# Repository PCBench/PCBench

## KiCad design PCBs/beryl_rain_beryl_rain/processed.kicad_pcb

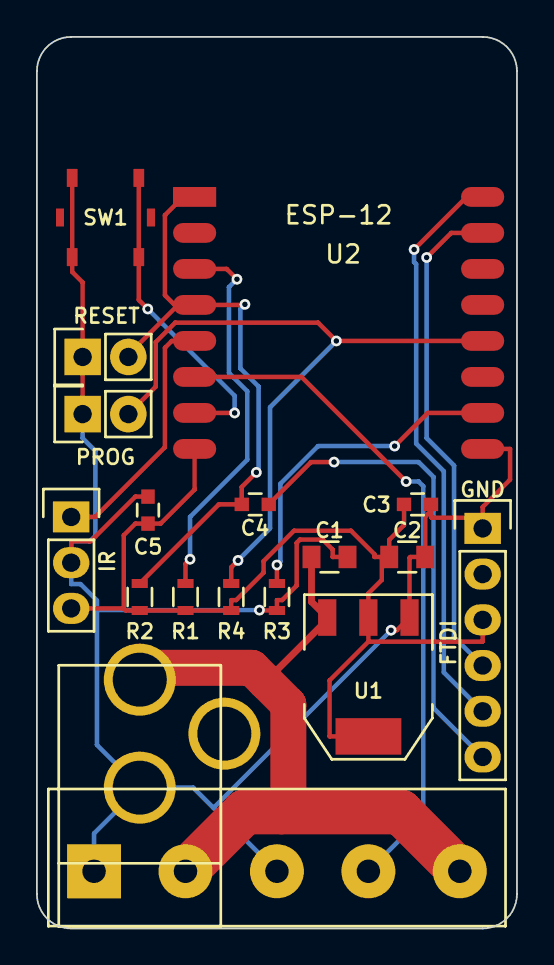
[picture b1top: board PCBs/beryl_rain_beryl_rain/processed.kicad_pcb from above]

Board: 2 copper layers, 26.7 x 49.5 mm, 18 parts (0 on the bottom side), 13 nets.

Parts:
C1, C2: CP; C_0805
C3, C4, C5: 0.1uF; C_0603
CON1: POWER; BARREL_JACK
P1: POWER; Terminal_Block_5.08mm_x5
P2: FTDI; Pin_Header_Straight_1x06
P3: IR; Pin_Header_Straight_1x03
P4: RESET; Pin_Header_Straight_1x02
P5: PROG; Pin_Header_Straight_1x02
R1, R2, R3, R4: 10K; R_0603
SW1: SWITCH; EVQPT5
U1: NCP1117ST33T3G; SOT-223
U2: ESP-12

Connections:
+3V3: C2.1, C3.1, C5.1, P2.3, P3.3, R1.1, R2.1, R4.1, U1.2, U1.4, U2.8
+5V: C1.1, CON1.1, P1.2, P1.5, U1.3
GND: C1.2, C2.2, C3.2, C5.2, CON1.2, P1.1, P1.3, P2.1, P3.2, P4.1, P5.1, R3.2, SW1.1, U1.1, U2.9
IR_DATA: P3.1, U2.5
LED_DATA: P1.4, U2.6
unnamed: C4.1, P2.6
unnamed: P5.2, R4.2, U2.12
unnamed: R1.2, U2.3
unnamed: R3.1, U2.10
unnamed: SW1.2, U2.7
RESET: C4.2, P4.2, R2.2, U2.1, U2.4
RX: P2.4, U2.15
TX: P2.5, U2.16

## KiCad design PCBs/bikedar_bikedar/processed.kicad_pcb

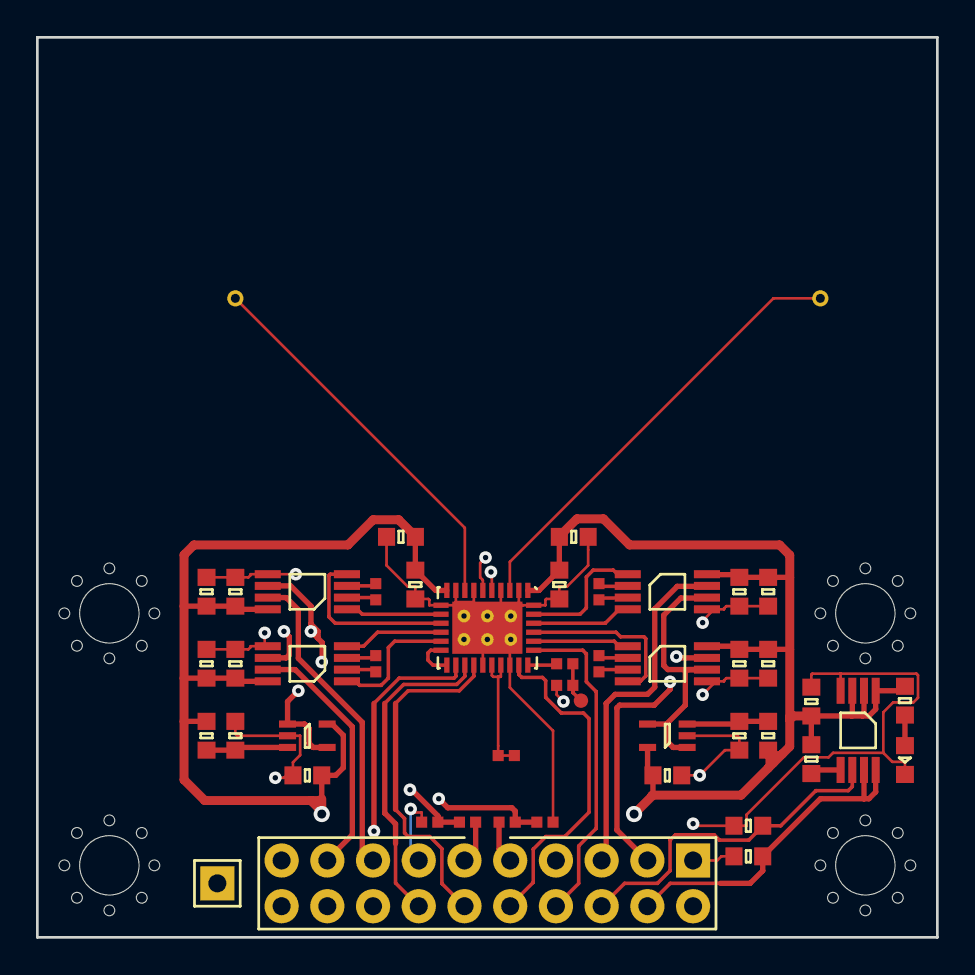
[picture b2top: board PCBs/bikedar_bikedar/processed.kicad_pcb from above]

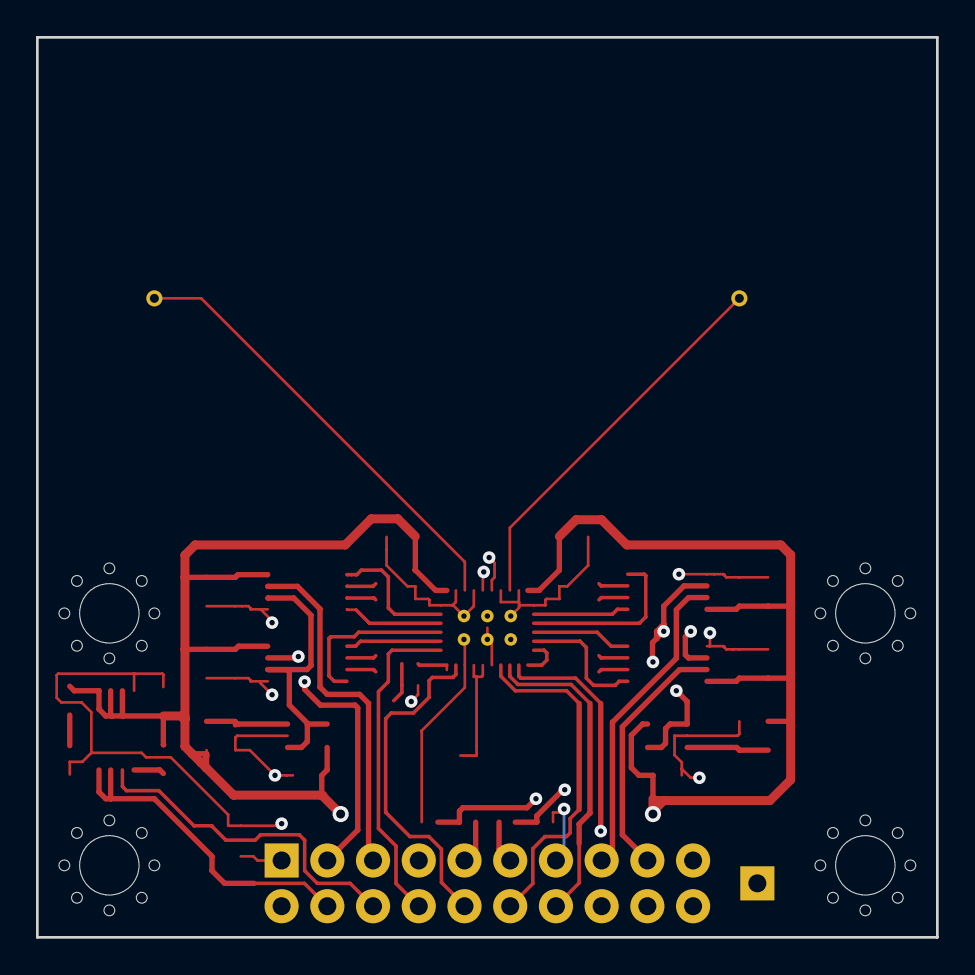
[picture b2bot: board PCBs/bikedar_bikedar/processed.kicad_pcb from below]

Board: 4 copper layers, 50.0 x 50.0 mm, 52 parts (2 on the bottom side), 45 nets.

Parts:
AE2, AE3: X0
C1, C3, C7, C18: 1µ; 0603
C2: 1n; 0603
C4, C15, C19, C20: 10µ; 0603
C5, C6: 100n; 0402
C8, C10, C11, C12, C13, C14, C16, C17: 100n; 0603
C9: 1n; 0402
D1: LED; 0603-LED
IC1: ADP3335; MSOP-8
IC2: BGT24MTR12; QFN-32-BGT24MTR
IC3, IC8: AD8541; SC-70-5
IC4, IC5, IC6, IC7: AD8226; MSOP-8
J1: CONN_02x10; DIL-254P-20
R1, R2, R13: 100; 0402
R3: 50; 0402
R4, R5, R10, R11, R12: 10k; 0603
R6, R7, R8, R9: 5k49; 0402
R14: 1k; 0603
TP1: TESTPAD
TP2: TESTPAD; SIL-254P-01
X1, X2, X3, X4: M3_MOUNT

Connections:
3v3: C2.2, C3.1, C4.1, C7.1, C8.1, C10.1, C11.1, C12.1, C13.1, C14.1, C15.1, C16.1, C17.1, C18.1, C19.1, C20.1, IC1.1, IC1.2, IC1.3, IC2.1, IC2.10, IC3.5, IC4.8, IC5.8, IC6.8, IC7.8, IC8.5, R4.1, R11.1, R14.1
/ANA: IC2.25, J1.10
/CLK: IC2.19, J1.14
/COARSE: J1.11, R2.1
/FINE: J1.9, R1.1
/FREQ: IC2.27, J1.8
/IFI1: IC4.7, J1.3
/IFI1_N: IC2.28, IC4.1
/IFI1_P: IC2.29, IC4.4
/IFI2: IC6.7, J1.17
/IFI2_N: IC2.15, IC6.1
/IFI2_P: IC2.14, IC6.4
/IFQ1: IC5.7, J1.5
/IFQ1_N: IC2.31, IC5.1
/IFQ1_P: IC2.30, IC5.4
/IFQ2: IC7.7, J1.15
/IFQ2_N: IC2.12, IC7.1
/IFQ2_P: IC2.13, IC7.4
/RX1: AE2.1, IC2.3
/RX2: AE3.1, IC2.8
/SI: IC2.20, J1.12
/TX: IC2.22, IC2.23, R13.1, R13.2
/VREF1: IC3.1, IC3.4, IC4.6, IC5.6
/VREF2: IC6.6, IC7.6, IC8.1, IC8.4
/~CS: IC2.18, J1.16
/~SD: IC1.6, J1.6, R10.1
GND: C1.2, C3.2, C4.2, C5.2, C6.1, C7.2, C8.2, C10.2, C11.2, C12.2, C13.2, C14.2, C15.2, C16.2, C17.2, C18.2, C19.2, C20.2, D1.1, IC1.4, IC2.2, IC2.4, IC2.7, IC2.9, IC2.11, IC2.21, IC2.24, IC2.32, IC2.EP, IC3.2, IC4.5, IC5.5, IC6.5, IC7.5, IC8.2, J1.1, J1.2, J1.7, J1.13, J1.18, J1.19, J1.20, R3.1, R5.2, R10.2, R12.2, TP2.1
unnamed: C2.1, IC1.5
unnamed: C5.1, IC2.5, R1.2
unnamed: C6.2, IC2.6, R2.2
unnamed: C9.1, R3.2, TP1.1
unnamed: C9.2, IC2.26
unnamed: D1.2, R14.2
unnamed: IC2.16, IC2.17
unnamed: IC3.3, R4.2, R5.1
unnamed: IC4.2, R6.2
unnamed: IC4.3, R6.1
unnamed: IC5.2, R7.2
unnamed: IC5.3, R7.1
unnamed: IC6.2, R8.2
unnamed: IC6.3, R8.1
unnamed: IC7.2, R9.2
unnamed: IC7.3, R9.1
unnamed: IC8.3, R11.2, R12.1
VBATT: C1.1, IC1.7, IC1.8, J1.4

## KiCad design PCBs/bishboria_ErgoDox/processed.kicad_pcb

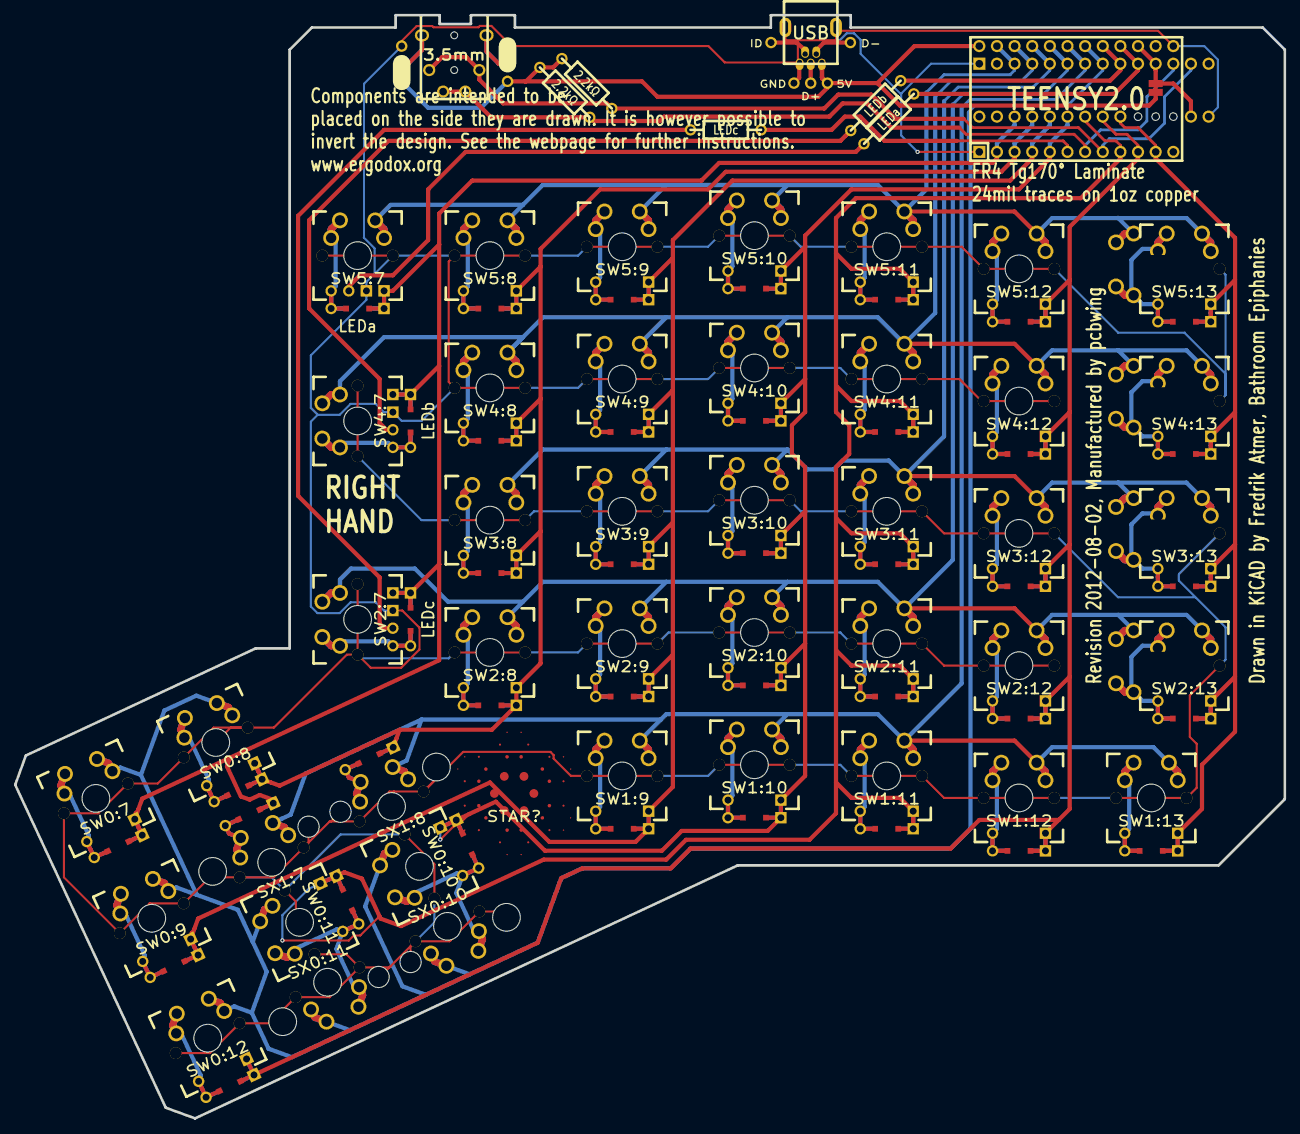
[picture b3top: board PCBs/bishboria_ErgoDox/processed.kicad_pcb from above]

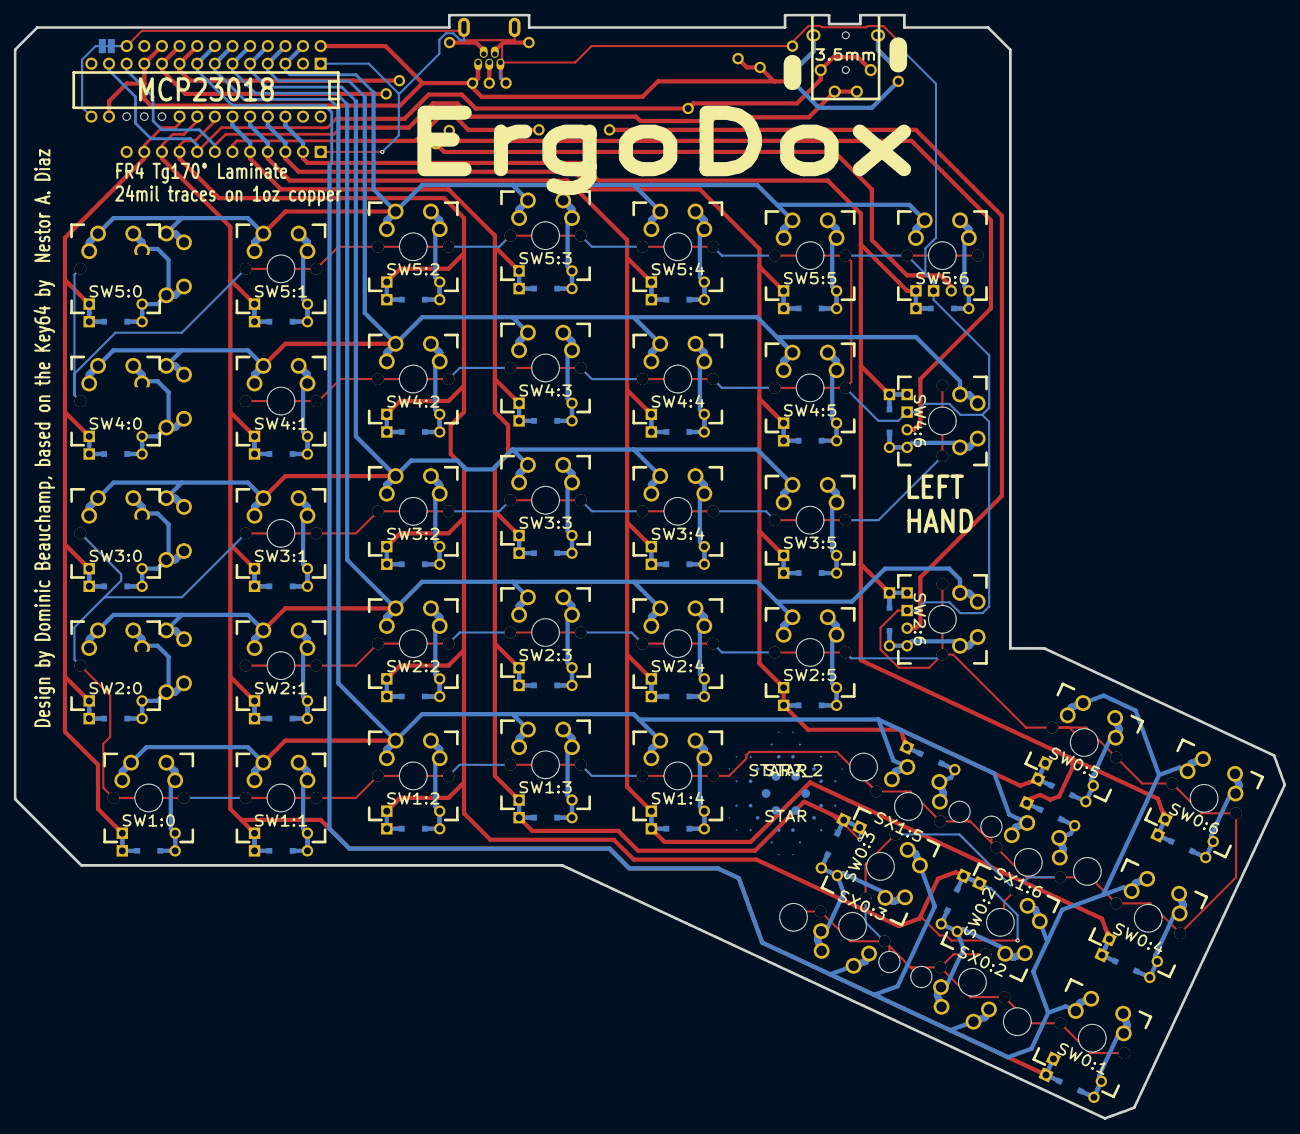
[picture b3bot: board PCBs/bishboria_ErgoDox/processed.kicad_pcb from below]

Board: 2 copper layers, 182.8 x 158.9 mm, 64 parts (4 on the bottom side), 65 nets.

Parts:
D1:7, D1:8: D; DIODE
J1: USB; USBMINImod
J2: 3.5mm; 4pin35mmAudio
J3, J4: JMP; 100PITCH1X3
JP1, JP2: JUMPER; GAP
LED_A1: LEDa; MX_LED
LED_B1: LEDb; MX_LED
LED_C1: LEDc; MX_LED
R1, R2: 2.2kΩ; RESISTOR
RA1: LEDa; RESISTOR
RB1: LEDb; RESISTOR
RC1: LEDc; RESISTOR
S1, S2: STAB200; STAB_PCB940
STAR?: STAR
STAR?_2: STAR
SW0:7: SW0:6; MX_FLIP_DIODE
SW0:8: SW0:5; MX_FLIP_DIODE
SW0:9: SW0:4; MX_FLIP_DIODE
SW0:10: SW0:3; MX_FLIP_DIODE
SW0:11: SW0:2; MX_FLIP_DIODE
SW0:12: SW0:1; MX_FLIP_DIODE
SW1:9: SW1:4; MX_FLIP_DIODE
SW1:10: SW1:3; MX_FLIP_DIODE
SW1:11: SW1:2; MX_FLIP_DIODE
SW1:12: SW1:1; MX_FLIP_DIODE
SW1:13: SW1:0; MX_FLIP_DIODE
SW2:7: SW2:6; MX_FLIP_DIODE
SW2:8: SW2:5; MX_FLIP_DIODE
SW2:9: SW2:4; MX_FLIP_DIODE
SW2:10: SW2:3; MX_FLIP_DIODE
SW2:11: SW2:2; MX_FLIP_DIODE
SW2:12: SW2:1; MX_FLIP_DIODE
SW2:13: SW2:0; MX_FLIP_XX
SW3:8: SW3:5; MX_FLIP_DIODE
SW3:9: SW3:4; MX_FLIP_DIODE
SW3:10: SW3:3; MX_FLIP_DIODE
SW3:11: SW3:2; MX_FLIP_DIODE
SW3:12: SW3:1; MX_FLIP_DIODE
SW3:13: SW3:0; MX_FLIP_XX
SW4:7: SW4:6; MX_FLIP_DIODE
SW4:8: SW4:5; MX_FLIP_DIODE
SW4:9: SW4:4; MX_FLIP_DIODE
SW4:10: SW4:3; MX_FLIP_DIODE
SW4:11: SW4:2; MX_FLIP_DIODE
SW4:12: SW4:1; MX_FLIP_DIODE
SW4:13: SW4:0; MX_FLIP_XX
SW5:7: SW5:6; MX_FLIP_DIODE
SW5:8: SW5:5; MX_FLIP_DIODE
SW5:9: SW5:4; MX_FLIP_DIODE
SW5:10: SW5:3; MX_FLIP_DIODE
SW5:11: SW5:2; MX_FLIP_DIODE
SW5:12: SW5:1; MX_FLIP_DIODE
SW5:13: SW5:0; MX_FLIP_XX
SX0:10: SX0:3; MX_FLIP
SX0:11: SX0:2; MX_FLIP
SX1:7: SX1:6; MX_FLIP
SX1:8: SX1:5; MX_FLIP
U1: TEENSY2.0; TEENSY_2.0
U2: MCP23018; DIP28_300

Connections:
/COL0: SW1:13.4, SW2:13.4, SW3:13.4, SW4:13.4, SW5:13.4, U1.11, U2.20
/COL1: SW0:12.4, SW1:12.4, SW2:12.4, SW3:12.4, SW4:12.4, SW5:12.4, U1.10, U2.21
/COL4: SW0:9.4, SW1:9.4, SW2:9.4, SW3:9.4, SW4:9.4, SW5:9.4, U1.4, U2.24
/COL5: D1:8.2, SW0:8.4, SW2:8.4, SW3:8.4, SW4:8.4, SW5:8.4, U1.3, U2.25
/COL6: D1:7.2, SW0:7.4, SW2:7.4, SW4:7.4, SW5:7.4, U1.2, U2.26
/COL10: SW0:10.4, SW1:10.4, SW2:10.4, SW3:10.4, SW4:10.4, SW5:10.4, U1.5, U2.23
/COL11: SW0:11.4, SW1:11.4, SW2:11.4, SW3:11.4, SW4:11.4, SW5:11.4, U1.9, U2.22
/LED_A: RA1.1, U1.21
/LED_B: RB1.1, U1.22
/LED_C: RC1.1, U1.6
/ROW0: SW0:7.1, SW0:8.1, SW0:9.1, SW0:10.1, SW0:11.1, SW0:12.1, SX0:10.1, SX0:11.1, U1.23, U2.8
/ROW1: SW1:9.1, SW1:10.1, SW1:11.1, SW1:12.1, SW1:13.1, SX1:7.1, SX1:8.1, U1.24, U2.7
/ROW2: SW2:7.1, SW2:8.1, SW2:9.1, SW2:10.1, SW2:11.1, SW2:12.1, SW2:13.1, U1.25, U2.6
/ROW3: SW3:8.1, SW3:9.1, SW3:10.1, SW3:11.1, SW3:12.1, SW3:13.1, U1.26, U2.5
/ROW4: SW4:7.1, SW4:8.1, SW4:9.1, SW4:10.1, SW4:11.1, SW4:12.1, SW4:13.1, U1.27, U2.4
/ROW5: SW5:7.1, SW5:8.1, SW5:9.1, SW5:10.1, SW5:11.1, SW5:12.1, SW5:13.1, U1.28, U2.3
/SCLM: J2.3, J2.5, R2.2, U1.7, U2.12
/SDAM: J2.2, J2.6, R1.2, U1.8, U2.13
GND: J1.5, J1.6, J3.3, J4.3, JP2.1, LED_A1.2, LED_B1.2, LED_C1.2, S1.0, S2.0, SW0:7.0, SW0:8.0, SW0:9.0, SW0:10.0, SW0:11.0, SW0:12.0, SW1:9.0, SW1:10.0, SW1:11.0, SW1:12.0, SW1:13.0, SW2:7.0, SW2:8.0, SW2:9.0, SW2:10.0, SW2:11.0, SW2:12.0, SW2:13.0, SW3:8.0, SW3:9.0, SW3:10.0, SW3:11.0, SW3:12.0, SW3:13.0, SW4:7.0, SW4:8.0, SW4:9.0, SW4:10.0, SW4:11.0, SW4:12.0, SW4:13.0, SW5:7.0, SW5:8.0, SW5:9.0, SW5:10.0, SW5:11.0, SW5:12.0, SW5:13.0, SX0:10.0, SX0:11.0, SX1:7.0, SX1:8.0, U1.1, U1.18, U2.1, U2.15
unnamed: J2.4, J4.2
unnamed: J2.1, J3.2
unnamed: SW5:12.2, SW5:12.3
unnamed: SW5:8.2, SW5:8.3
unnamed: SW5:7.2, SW5:7.3
unnamed: D1:8.1, SX1:8.2
unnamed: SW5:9.2, SW5:9.3
unnamed: SW5:10.2, SW5:10.3
unnamed: SW5:11.2, SW5:11.3
unnamed: SW1:9.2, SW1:9.3
unnamed: SW0:10.2, SW0:10.3, SX0:10.2
unnamed: D1:7.1, SX1:7.2
unnamed: SW2:10.2, SW2:10.3
unnamed: SW3:9.2, SW3:9.3
unnamed: SW3:8.2, SW3:8.3
unnamed: SW2:7.2, SW2:7.3
unnamed: SW2:8.2, SW2:8.3
unnamed: SW2:9.2, SW2:9.3
unnamed: SW2:11.2, SW2:11.3
unnamed: SW1:11.2, SW1:11.3
unnamed: SW1:10.2, SW1:10.3
unnamed: SW2:12.2, SW2:12.3
unnamed: SW5:13.2, SW5:13.3
unnamed: SW4:9.2, SW4:9.3
unnamed: SW4:11.2, SW4:11.3
unnamed: SW4:12.2, SW4:12.3
unnamed: SW2:13.2, SW2:13.3
unnamed: SW4:13.2, SW4:13.3
unnamed: SW3:13.2, SW3:13.3
unnamed: SW3:12.2, SW3:12.3
unnamed: SW3:11.2, SW3:11.3
unnamed: SW3:10.2, SW3:10.3
unnamed: SW0:8.2, SW0:8.3
unnamed: SW1:13.2, SW1:13.3
unnamed: SW1:12.2, SW1:12.3
unnamed: SW0:12.2, SW0:12.3
unnamed: SW0:9.2, SW0:9.3
unnamed: SW0:7.2, SW0:7.3
unnamed: SW4:7.2, SW4:7.3
unnamed: SW4:8.2, SW4:8.3
unnamed: SW4:10.2, SW4:10.3
unnamed: LED_C1.1, RC1.2
unnamed: LED_B1.1, RB1.2
unnamed: LED_A1.1, RA1.2
unnamed: SW0:11.2, SW0:11.3, SX0:11.2
VCC: J1.1, J3.1, J4.1, JP1.1, R1.1, R2.1, U1.20, U1.29, U2.11, U2.16

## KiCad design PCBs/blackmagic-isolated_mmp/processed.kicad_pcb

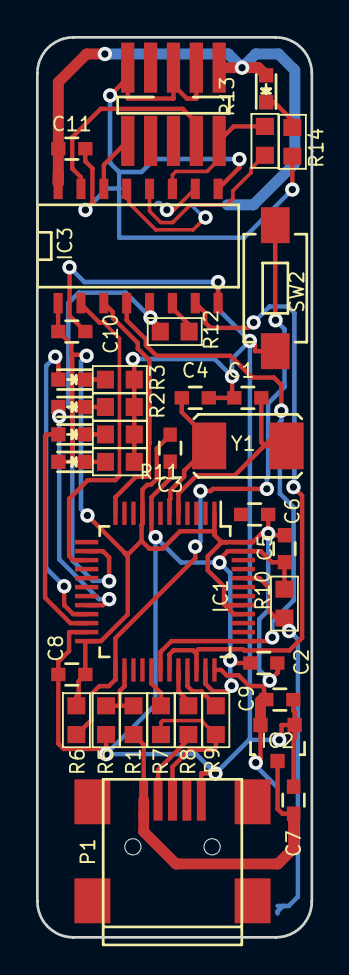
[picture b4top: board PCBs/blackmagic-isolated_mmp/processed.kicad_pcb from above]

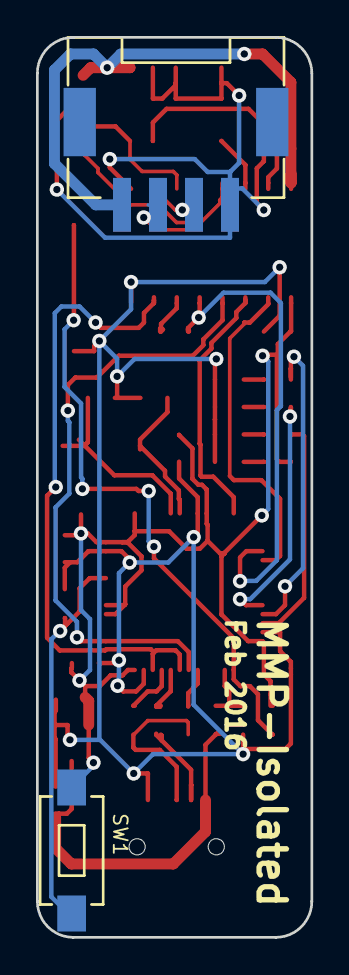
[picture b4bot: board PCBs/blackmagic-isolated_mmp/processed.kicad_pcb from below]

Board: 2 copper layers, 15.2 x 50.0 mm, 39 parts (2 on the bottom side), 35 nets.

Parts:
C1, C4: C_Small; C_0603
C2, C3, C5, C6, C10, C11: 100n; C_0603
C7, C9: 4.7u; C_0603
C8: 1u; C_0603
D1, D2, D3, D4, D5: LED; LED-0603
IC1: STM32F103C; LQFP-48_7x7mm_Pitch0.5mm
IC2: MCP1700-33; SOT-23
IC3: SI8662; SO-16-N
J1: SWD; FTSH-105-01-L-DV-K
P1: USB_B; USB_Mini-B
P2: CONN_01X04; SM04B-PASS
R1, R12, R13: 4.7k; C0603-N
R2, R3, R4, R11, R14: 330; C0603-N
R5, R6, R10: 10k; C0603-N
R7: 1.5k; C0603-N
R8, R9: 22; C0603-N
SW1, SW2: SW_PUSH; SW_SPST_EVQPE1
Y1: Crystal_Small; ABM7

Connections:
+3.3VP: C11.1, D5.2, IC3.16, J1.1, P2.4
+3V3: C2.1, C3.1, C5.1, C6.1, C8.1, C9.1, C10.1, D4.2, IC1.1, IC1.9, IC1.24, IC1.36, IC1.40, IC1.41, IC1.48, IC2.2, IC3.1, R6.2, SW1.1
/H_SWCLK: IC1.30, IC1.37, IC3.4
/H_SWDIO: IC1.31, IC1.34, IC3.7
/LED0: D1.2, IC1.20
/LED1: D2.2, IC1.21
/LED2: D3.2, IC1.22
/RST: IC1.12, IC3.3
/Rx: IC3.10, P2.2
/SWCLK: IC1.15, IC3.2
/SWDIO: IC1.14, IC3.5, R12.1
/Tx: IC3.13, P2.3
/Vbus: C7.1, IC2.3, P1.1, R1.1
GND: C1.2, C2.2, C3.2, C4.2, C5.2, C7.2, C8.2, C9.2, C10.2, IC1.8, IC1.23, IC1.35, IC1.47, IC2.1, IC3.8, P1.5, R2.2, R3.2, R4.2, R5.2, R10.1, R11.2, SW2.2
GNDREF: C11.2, IC3.9, J1.3, J1.5, J1.9, P2.1, R14.2
unnamed: C1.1, IC1.5, Y1.1
unnamed: C4.1, IC1.6, Y1.2
unnamed: D1.1, R2.1
unnamed: D2.1, R3.1
unnamed: D3.1, R4.1
unnamed: D4.1, R11.1
unnamed: D5.1, R14.1
unnamed: IC1.25, R6.1, SW2.1
unnamed: IC1.26, R1.2, R5.1
unnamed: IC1.29, R7.1
unnamed: IC1.32, R8.1
unnamed: IC1.33, R9.2
unnamed: IC1.44, R10.2, SW1.2
unnamed: IC3.6, R12.2
unnamed: IC3.11, J1.2, R13.2
unnamed: IC3.12, R13.1
unnamed: IC3.14, J1.10
unnamed: IC3.15, J1.4
unnamed: P1.2, R8.2
unnamed: P1.3, R7.2, R9.1

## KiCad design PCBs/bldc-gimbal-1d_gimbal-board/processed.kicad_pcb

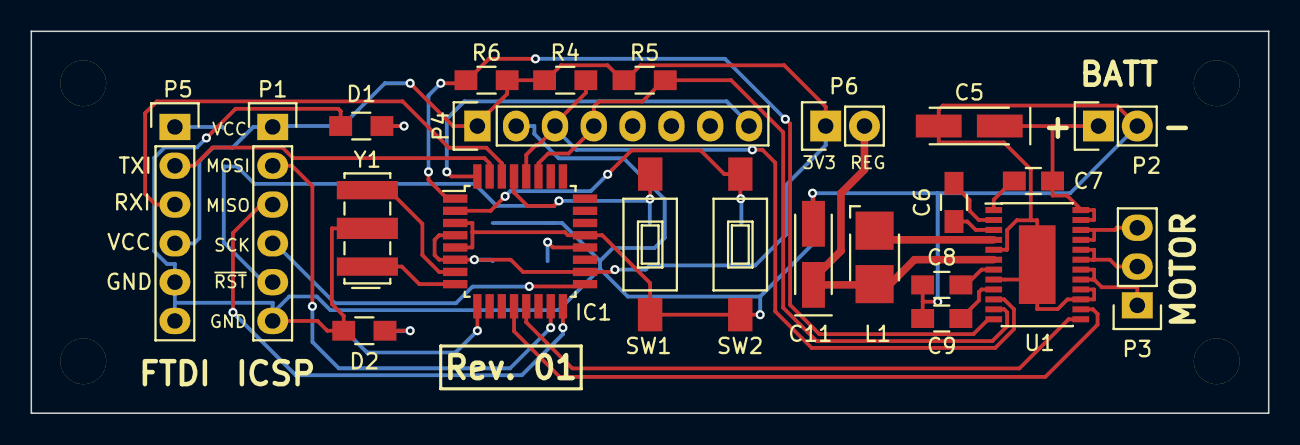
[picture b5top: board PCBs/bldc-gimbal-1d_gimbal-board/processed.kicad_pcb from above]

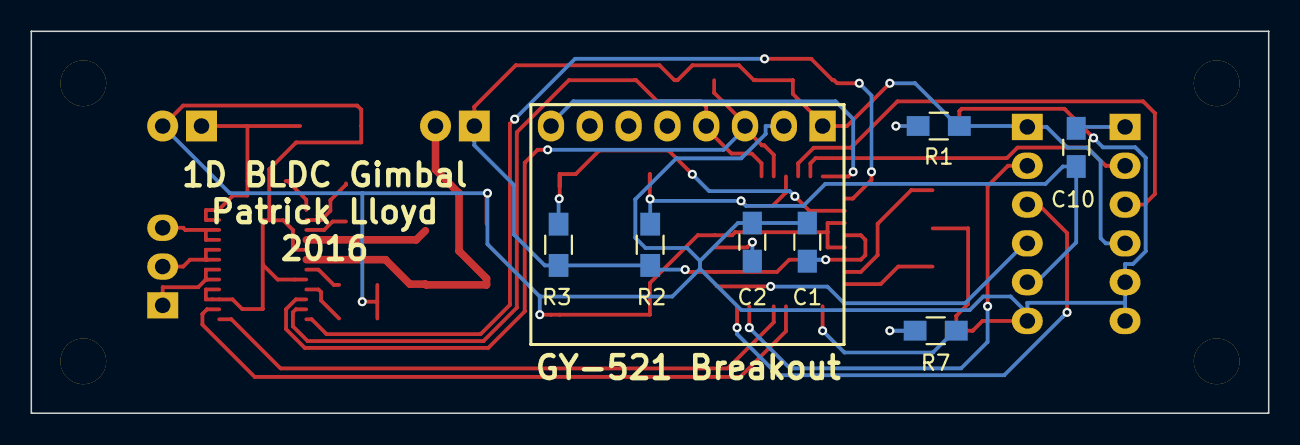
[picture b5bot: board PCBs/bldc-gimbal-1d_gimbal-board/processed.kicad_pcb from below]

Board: 2 copper layers, 81.0 x 25.0 mm, 34 parts (7 on the bottom side), 33 nets.

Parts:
C1, C2, C6, C7, C10: 0.1uF; C_0805_HandSoldering
C5, C11: 10uF; TantalC_SizeA_EIA-3216_HandSoldering
C8, C9: 1uF; C_0805_HandSoldering
D1: RED; R_0805_HandSoldering
D2: GRN; R_0805_HandSoldering
H1, H2, H3, H4: CONN_01X01; MountingHole_3mm
IC1: ATMEGA328P-A; TQFP-32_7x7mm_Pitch0.8mm
L1: 47uH; Inductor_1212
P1: ICSP; Pin_Header_Straight_1x06
P2: BATT; Pin_Header_Straight_1x02
P3: MOTOR; Pin_Header_Straight_1x03
P4: IMU; Pin_Header_Straight_1x08
P5: FTDI; Pin_Header_Straight_1x06
P6: 3V3_CONN; Pin_Header_Straight_1x02
R1, R7: 330; R_0805_HandSoldering
R2, R3: 10K; R_0805_HandSoldering
R4, R5, R6: DNP; R_0805_HandSoldering
SW1, SW2: SW_PUSH; SW_SPST_FSMSM
U1: DRV10975; TSSOP-24_4.4x7.8mm_Pitch0.65mm_EP
Y1: Resonator; Resonator_7.2x3mm

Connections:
+3V3: C1.1, IC1.4, IC1.6, IC1.18, P1.1, P4.1, P5.4, P6.1, R1.1, R2.2, R3.2, R4.1, R5.1, R6.1
+BATT: C5.1, C7.2, P2.1, U1.23, U1.24
/ICSP_MISO: IC1.16, P1.3
/ICSP_MOSI: IC1.15, P1.2
/ICSP_SCK: IC1.17, P1.4
/IMU_INT: IC1.32, P4.8
/M_DIR: IC1.12, U1.14
/M_FG: IC1.1, R6.2, U1.12
/M_PHASE_U: P3.1, U1.17, U1.18
/M_PHASE_V: P3.2, U1.19, U1.20
/M_PHASE_W: P3.3, U1.21, U1.22
/M_SPEED: IC1.13, U1.13
/REG_OUT: C11.1, L1.2, P6.2, U1.6
/RESET: C10.1, IC1.29, P1.5, R2.1, SW1.1
/SCL: IC1.28, P4.3, R4.2, U1.10
/SDA: IC1.27, P4.4, R5.2, U1.11
/USART_DTR: C10.2, P5.1
/USART_RX: IC1.30, P5.3
/USART_TX: IC1.31, P5.2
/V3P3: C9.1, U1.9
GND: C1.2, C2.2, C5.2, C8.2, C9.2, C11.2, D1.1, D2.1, IC1.3, IC1.5, IC1.21, P1.6, P2.2, P4.2, P5.5, P5.6, SW1.2, SW2.2, U1.5, U1.8, U1.15, U1.16, U1.EP, Y1.2
unnamed: C2.1, IC1.20
unnamed: C6.1, U1.3
unnamed: C6.2, U1.2
unnamed: C7.1, U1.1
unnamed: C8.1, U1.7
unnamed: D1.2, R1.2
unnamed: D2.2, R7.2
unnamed: IC1.2, R3.1, SW2.1
unnamed: IC1.7, Y1.3
unnamed: IC1.8, Y1.1
unnamed: IC1.9, R7.1
unnamed: L1.1, U1.4

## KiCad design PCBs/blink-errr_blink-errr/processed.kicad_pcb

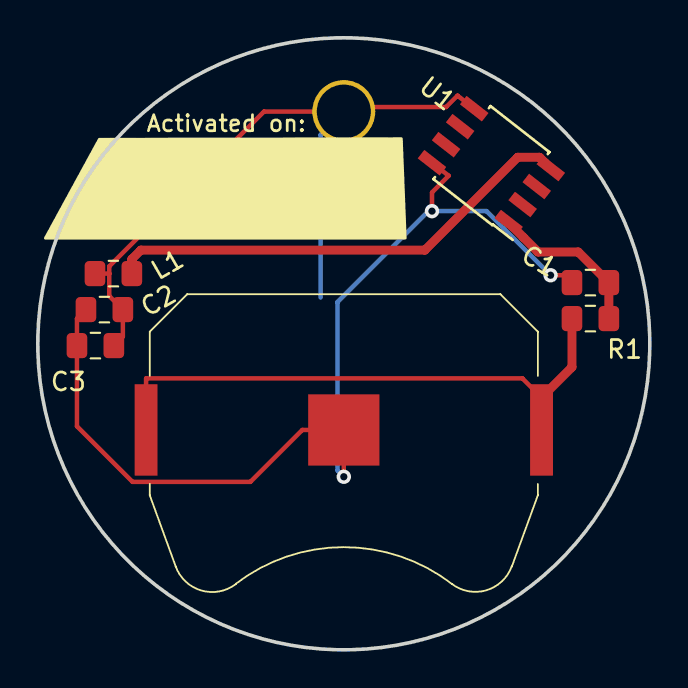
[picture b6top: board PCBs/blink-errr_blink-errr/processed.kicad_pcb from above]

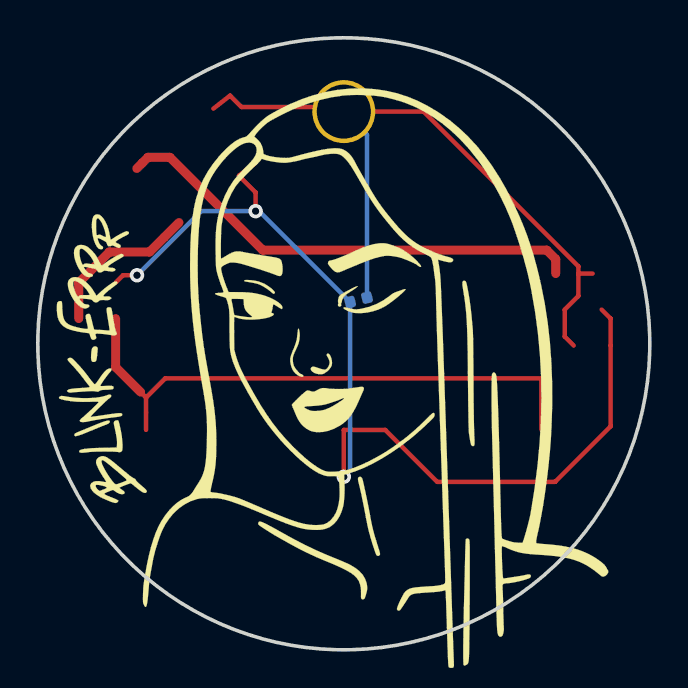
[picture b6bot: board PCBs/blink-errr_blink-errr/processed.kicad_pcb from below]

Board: 2 copper layers, 34.0 x 34.0 mm, 9 parts (2 on the bottom side), 5 nets.

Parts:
BT1: Battery_Cell; BatteryHolder_Keystone_3034_1x20mm
C1, C2, C3: C; C_0805_2012Metric_Pad1.15x1.40mm_HandSolder
D1: LED; LED_0402_1005Metric
H1: MountingHole; MountingHole_3.2mm_M3_DIN965_Pad
L1: L; L_0805_2012Metric_Pad1.15x1.40mm_HandSolder
R1: R; R_0805_2012Metric_Pad1.15x1.40mm_HandSolder
U1: ATtiny202-SS; SOIC-8_3.9x4.9mm_P1.27mm

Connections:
FEEDBACK: C2.1, C3.1, D1.2, H1.1, L1.2, U1.5
GND: BT1.2, C1.2, C2.2, C3.2, D1.1, U1.8
unnamed: BT1.1, R1.2
unnamed: L1.1, U1.4
VCC: C1.1, R1.1, U1.1
